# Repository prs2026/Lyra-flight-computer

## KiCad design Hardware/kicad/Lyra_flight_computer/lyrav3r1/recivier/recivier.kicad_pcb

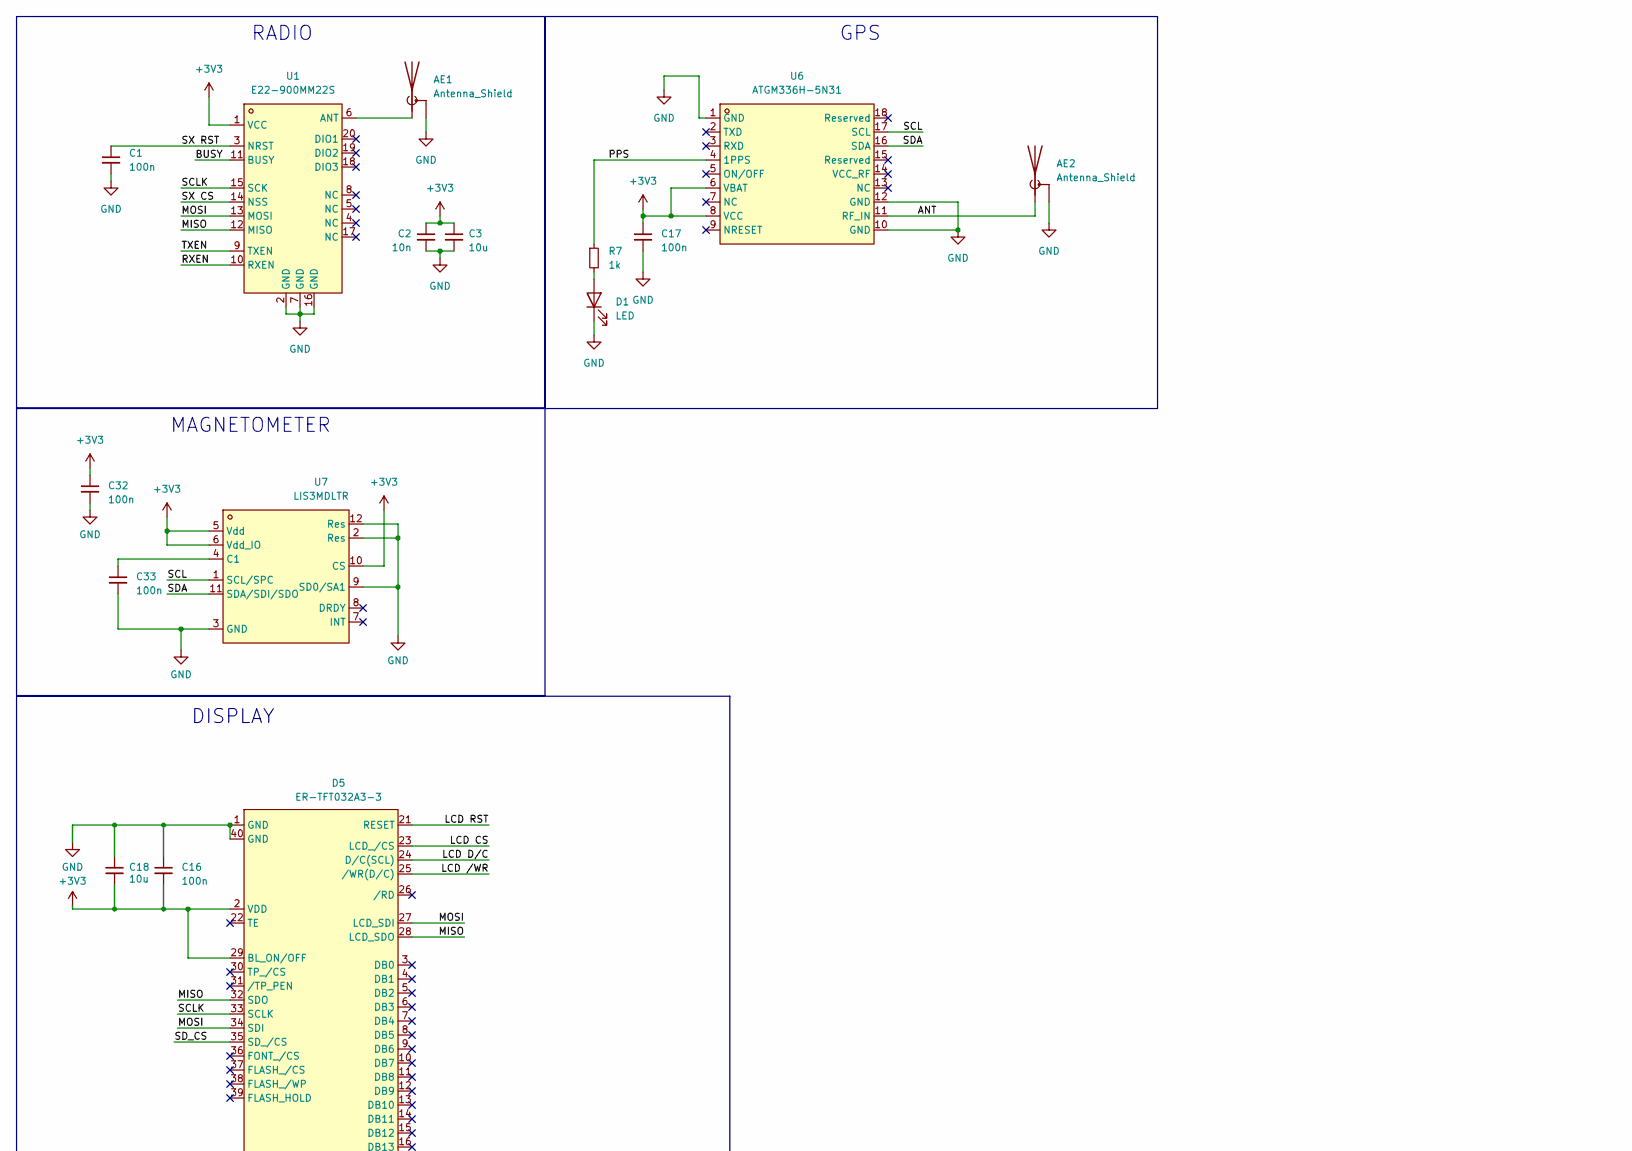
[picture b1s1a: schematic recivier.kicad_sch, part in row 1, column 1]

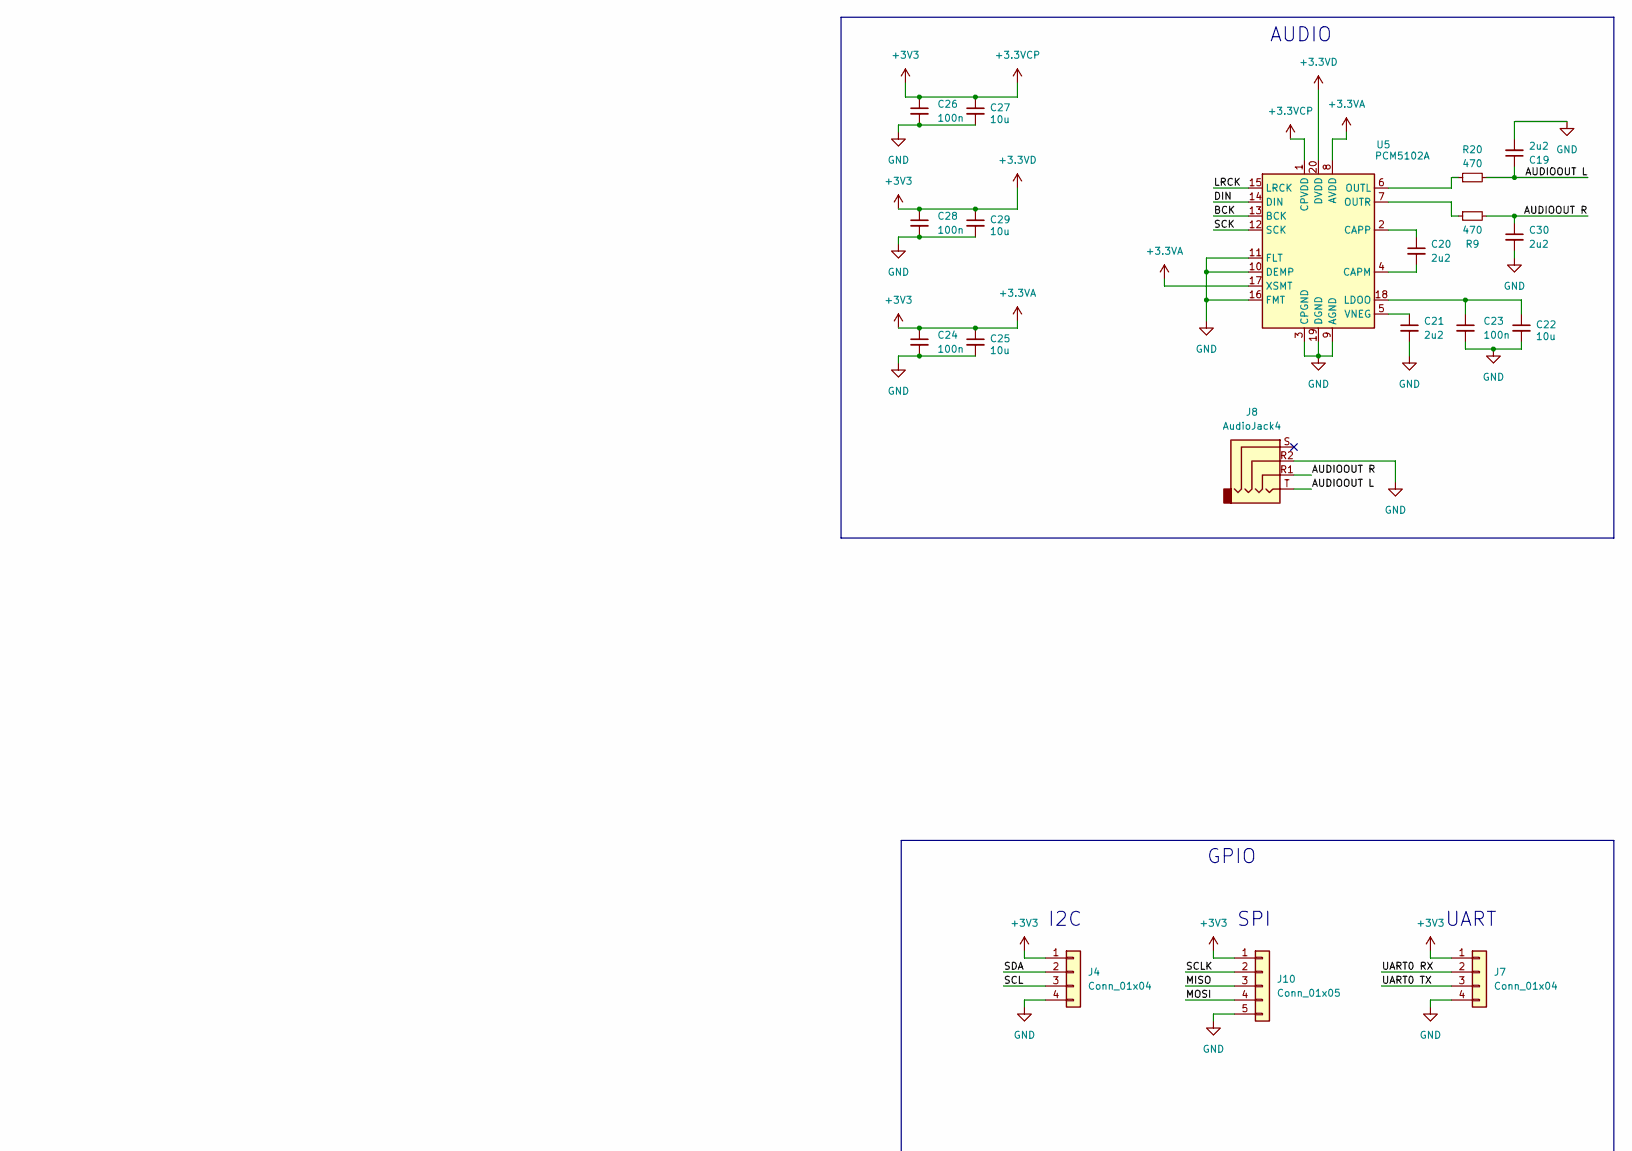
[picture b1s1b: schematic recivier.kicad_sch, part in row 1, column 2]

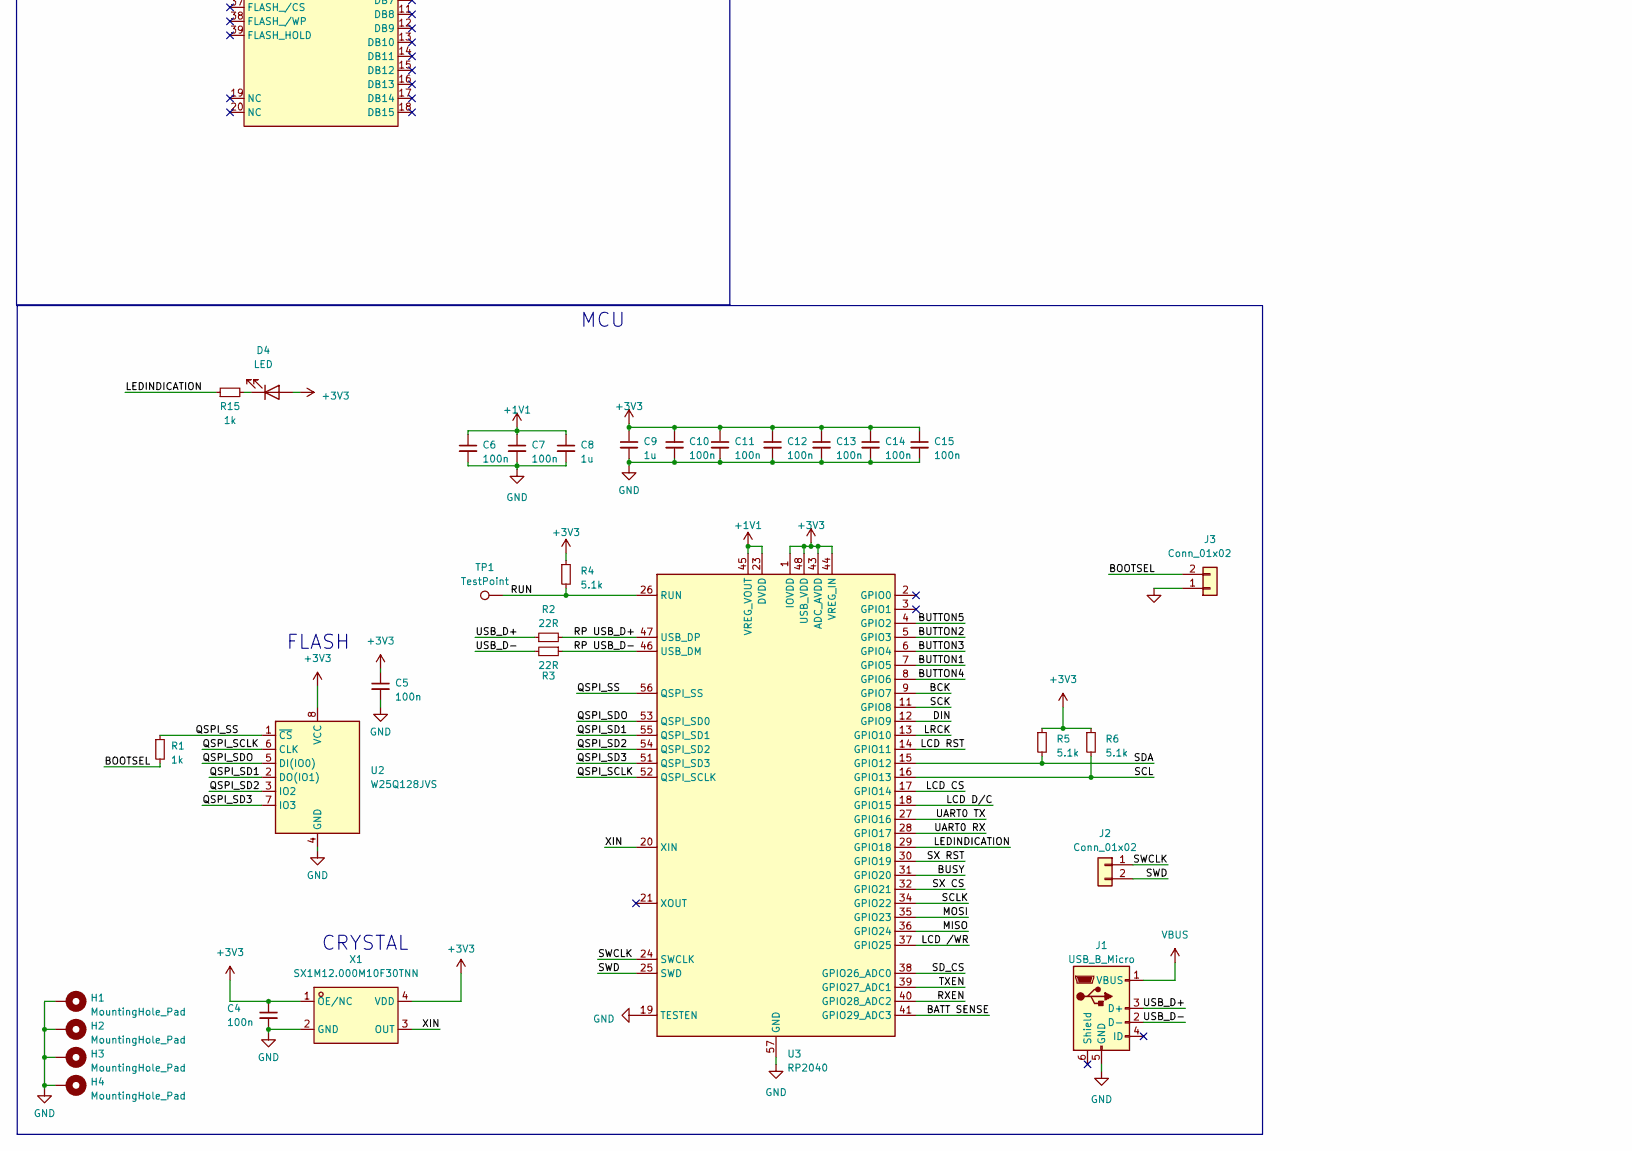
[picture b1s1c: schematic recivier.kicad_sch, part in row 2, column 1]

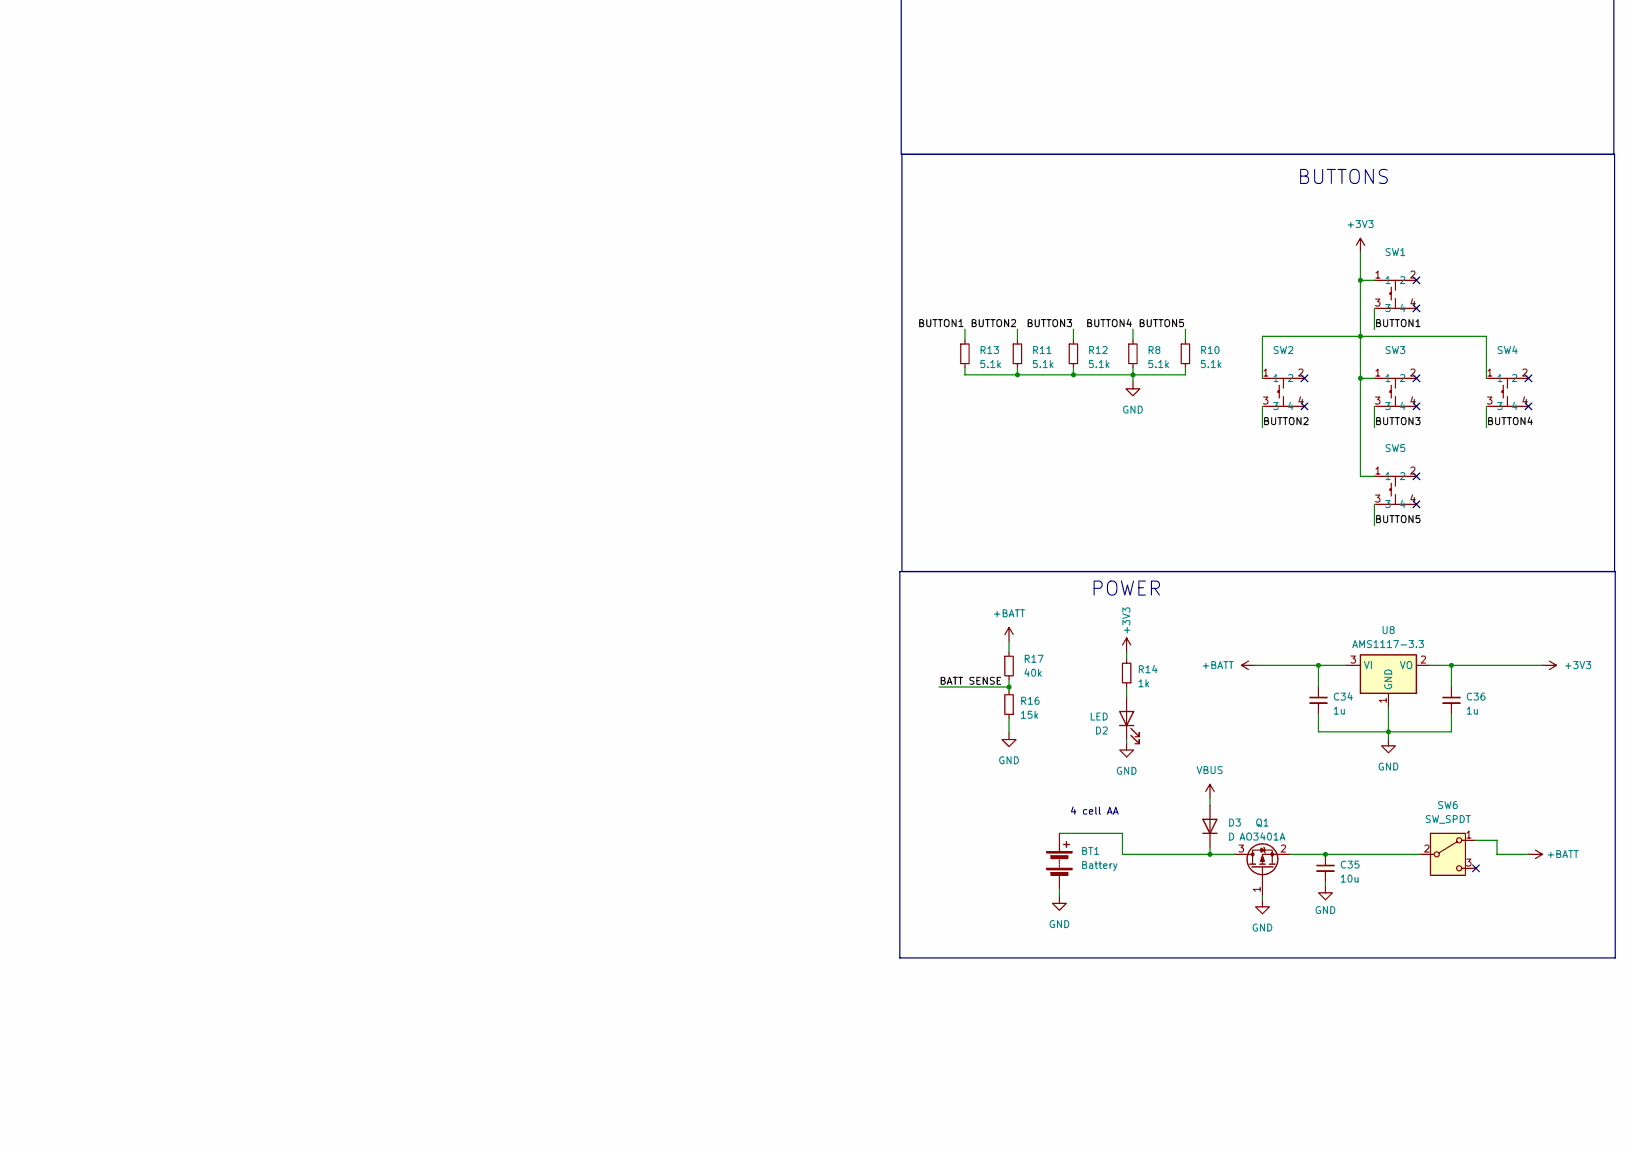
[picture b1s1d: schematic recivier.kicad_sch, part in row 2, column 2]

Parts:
AE1: Antenna_Shield; CONN-SMD_KH-SMA-KE8-G; LCSC Part C530661
AE2: Antenna_Shield; ANT-SMD_1909763-1; LCSC Part C392444
BT1: Battery; 12BH349GR
C1, C4, C5, C6, C7, C10, C11, C12, C13, C14, C15, C16, C17, C23, C24, C26, C28, C32, C33: 100n; C_0402_1005Metric; LCSC Part C1525
C2: 10n; C_0402_1005Metric; LCSC Part C15195
C3, C18, C22, C25, C27, C29, C35: 10u; C_0603_1608Metric; LCSC Part C96446
C8, C9, C34, C36: 1u; C_0402_1005Metric; LCSC Part C52923
C19, C20, C21, C30: 2u2; C_0603_1608Metric; LCSC Part C23630
D1, D2, D4: LED; LED_0805_2012Metric; LCSC Part C2297
D3: D; D_SOD-123; LCSC Part C64898
D5: ER-TFT032A3-3; R-TFT032IPS-3.2
H1, H2, H3, H4: MountingHole_Pad; MountingHole_3.2mm_M3_DIN965_Pad
J1: USB_B_Micro; MICRO-USB-SMD_U254-051T-4BHJ25-F2S; LCSC Part C381143
J2: Conn_01x02; SolderJumper-2_P1.3mm_Open_Pad1.0x1.5mm
J3: Conn_01x02; SolderJumper-2_P1.3mm_Open_RoundedPad1.0x1.5mm
J4, J7: Conn_01x04; PinHeader_1x04_P2.54mm_Horizontal
J8: AudioJack4; AUDIO-SMD_PJ-320D; LCSC Part C521460
J10: Conn_01x05; PinHeader_1x05_P2.54mm_Horizontal
Q1: AO3401A; SOT-23; LCSC Part C15127
R1, R7, R14, R15: 1k; R_0402_1005Metric; LCSC Part C11702
R2, R3: 22R; R_0402_1005Metric; LCSC Part C25092
R4, R5, R6, R8, R10, R11, R12, R13: 5.1k; R_0402_1005Metric; LCSC Part C25905
R9, R20: 470; R_0402_1005Metric; LCSC Part C25117
R16: 15k; R_0402_1005Metric; LCSC Part C25756
R17: 40k; R_0402_1005Metric; LCSC Part C25086
SW1, SW2, SW3, SW4, SW5: K2-1102DP-L3SW-04; SW-TH_4P-L6.0-W6.0-P4.50-LS6.5; LCSC Part C493026
SW6: SW_SPDT; SW-TH_SK12D07VG4; LCSC Part C393937
TP1: TestPoint; TestPoint_Pad_1.0x1.0mm
U1: E22-900MM22S; WIRELM-SMD_E22-400MM22S
U2: W25Q128JVS; SOIC-8_5.23x5.23mm_P1.27mm; LCSC Part C97521
U3: RP2040; QFN-56-1EP_7x7mm_P0.4mm_EP3.2x3.2mm; LCSC Part C2040
U5: PCM5102A; TSSOP-20_4.4x6.5mm_P0.65mm; LCSC Part C107671
U6: ATGM336H-5N31; GPSM-SMD_ATGM336H-TR; LCSC Part C90770
U7: LIS3MDLTR; LGA-12_L2.0-W2.0-P0.50-BL; LCSC Part C478483
U8: AMS1117-3.3; SOT-223-3_TabPin2; LCSC Part C6186
X1: SX1M12.000M10F30TNN; OSC-SMD_4P-L2.0-W1.6-BL; LCSC Part C2901608

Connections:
+1V1: C6.1, C7.1, C8.1, U3.23 (DVDD), U3.45 (VREG_VOUT), U3.50 (DVDD)
+3.3VA: C2.1, C3.1, C4.1, C5.1, C9.1, C10.1, C11.1, C12.1, C13.1, C14.1, C15.1, C16.2, C17.1, C18.2, C24.1, C25.1, C26.1, C27.1, C28.1, C29.1, C32.1, C36.1, D4.2 (A), D5.2 (VDD), D5.29 (BL_ON/OFF), J4.1, J7.1, J10.1, R4.1, R5.1, R6.1, R14.2, SW1.1, SW2.1, SW3.1, SW4.1, SW5.1, U1.1 (VCC), U2.8 (VCC), U3.1 (IOVDD), U3.10 (IOVDD), U3.22 (IOVDD), U3.33 (IOVDD), U3.42 (IOVDD), U3.43 (ADC_AVDD), U3.44 (VREG_IN), U3.48 (USB_VDD), U3.49 (IOVDD), U5.1 (CPVDD), U5.8 (AVDD), U5.17 (XSMT), U5.20 (DVDD), U6.6 (VBAT), U6.8 (VCC), U7.5 (Vdd), U7.6 (Vdd_IO), U7.10 (CS), U8.2 (VO), X1.1 (OE/NC), X1.4 (VDD)
+BATT: C34.1, R17.1, SW6.1 (A), U8.3 (VI)
/ANT: AE2.1 (A), U6.11 (RF_IN)
/AUDIOOUT L: C19.1, J8.T, R20.2
/AUDIOOUT R: C30.1, J8.R1, R9.2
/BATT SENSE: R16.2, R17.2, U3.41 (GPIO29_ADC3)
/BCK: U3.9 (GPIO7), U5.13 (BCK)
/BOOTSEL: J3.2, R1.2
/BUSY: U1.11 (BUSY), U3.31 (GPIO20)
/BUTTON1: R13.1, SW1.3, U3.7 (GPIO5)
/BUTTON2: R11.1, SW2.3, U3.5 (GPIO3)
/BUTTON3: R12.1, SW3.3, U3.6 (GPIO4)
/BUTTON4: R8.1, SW4.3, U3.8 (GPIO6)
/BUTTON5: R10.1, SW5.3, U3.4 (GPIO2)
/DIN: U3.12 (GPIO9), U5.14 (DIN)
/LCD CS: D5.23 (LCD_/CS), U3.17 (GPIO14)
/LCD D/C: D5.24 (D/C(SCL)), U3.18 (GPIO15)
/LCD RST: D5.21 (RESET), U3.14 (GPIO11)
/LCD /WR: D5.25 (/WR(D/C)), U3.37 (GPIO25)
/LEDINDICATION: R15.1, U3.29 (GPIO18)
/LRCK: U3.13 (GPIO10), U5.15 (LRCK)
/MISO: D5.28 (LCD_SDO), D5.32 (SDO), J10.3, U1.12 (MISO), U3.36 (GPIO24)
/MOSI: D5.27 (LCD_SDI), D5.34 (SDI), J10.4, U1.13 (MOSI), U3.35 (GPIO23)
/PPS: R7.1, U6.4 (1PPS)
/QSPI_SCLK: U2.6 (CLK), U3.52 (QSPI_SCLK)
/QSPI_SD1: U2.2 (DO(IO1)), U3.55 (QSPI_SD1)
/QSPI_SD2: U2.3 (IO2), U3.54 (QSPI_SD2)
/QSPI_SD3: U2.7 (IO3), U3.51 (QSPI_SD3)
/QSPI_SDO: U2.5 (DI(IO0)), U3.53 (QSPI_SD0)
/QSPI_SS: R1.1, U2.1 (~CS), U3.56 (QSPI_SS)
/RP USB_D+: R2.2, U3.47 (USB_DP)
/RP USB_D-: R3.1, U3.46 (USB_DM)
/RUN: R4.2, TP1.1, U3.26 (RUN)
/RXEN: U1.10 (RXEN), U3.40 (GPIO28_ADC2)
/SCK: U3.11 (GPIO8), U5.12 (SCK)
/SCL: J4.3, R6.2, U3.16 (GPIO13), U6.17 (SCL), U7.1 (SCL/SPC)
/SCLK: D5.33 (SCLK), J10.2, U1.15 (SCK), U3.34 (GPIO22)
/SDA: J4.2, R5.2, U3.15 (GPIO12), U6.16 (SDA), U7.11 (SDA/SDI/SDO)
/SD_CS: D5.35 (SD_/CS), U3.38 (GPIO26_ADC0)
/SWCLK: J2.1, U3.24 (SWCLK)
/SWD: J2.2, U3.25 (SWD)
/SX CS: U1.14 (NSS), U3.32 (GPIO21)
/SX RST: C1.1, U1.3 (NRST), U3.30 (GPIO19)
/TXEN: U1.9 (TXEN), U3.39 (GPIO27_ADC1)
/UART0 RX: J7.2, U3.28 (GPIO17)
/UART0 TX: J7.3, U3.27 (GPIO16)
/USB_D+: J1.3 (D+), R2.1
/USB_D-: J1.2 (D-), R3.2
/XIN: U3.20 (XIN), X1.3 (OUT)
GND: AE1.2 (Shield), AE2.2 (Shield), BT1.2 (-), C1.2, C2.2, C3.2, C4.2, C5.2, C6.2, C7.2, C8.2, C9.2, C10.2, C11.2, C12.2, C13.2, C14.2, C15.2, C16.1, C17.2, C18.1, C19.2, C21.2, C22.2, C23.2, C24.2, C25.2, C26.2, C27.2, C28.2, C29.2, C30.2, C32.2, C33.2, C34.2, C35.2, C36.2, D1.1 (K), D2.1 (K), D5.1 (GND), D5.40 (GND), H1.1, H2.1, H3.1, H4.1, J1.5 (GND), J3.1, J4.4, J7.4, J8.R2, J10.5, Q1.1 (G), R8.2, R10.2, R11.2, R12.2, R13.2, R16.1, U1.2 (GND), U1.7 (GND), U1.16 (GND), U2.4 (GND), U3.19 (TESTEN), U3.57 (GND), U5.3 (CPGND), U5.9 (AGND), U5.10 (DEMP), U5.11 (FLT), U5.16 (FMT), U5.19 (DGND), U6.1 (GND), U6.10 (GND), U6.12 (GND), U7.2 (Res), U7.3 (GND), U7.9 (SD0/SA1), U7.12 (Res), U8.1 (GND), X1.2 (GND)
unnamed: AE1.1 (A), U1.6 (ANT)
unnamed: BT1.1 (+), D3.1 (K), Q1.3 (D)
unnamed: D1.2 (A), R7.2
unnamed: D2.2 (A), R14.1
unnamed: D4.1 (K), R15.2
unnamed: C35.1, Q1.2 (S), SW6.2 (B)
unnamed: C20.2, U5.4 (CAPM)
unnamed: C20.1, U5.2 (CAPP)
unnamed: C22.1, C23.1, U5.18 (LDOO)
unnamed: R20.1, U5.6 (OUTL)
unnamed: R9.1, U5.7 (OUTR)
unnamed: C21.1, U5.5 (VNEG)
unnamed: C33.1, U7.4 (C1)
VBUS: D3.2 (A), J1.1 (VBUS)

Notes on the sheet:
FLASH
4 cell AA
I2C
AUDIO
MAGNETOMETER
CRYSTAL
POWER
BUTTONS
GPS
RADIO
GPIO
DISPLAY
UART
SPI
MCU

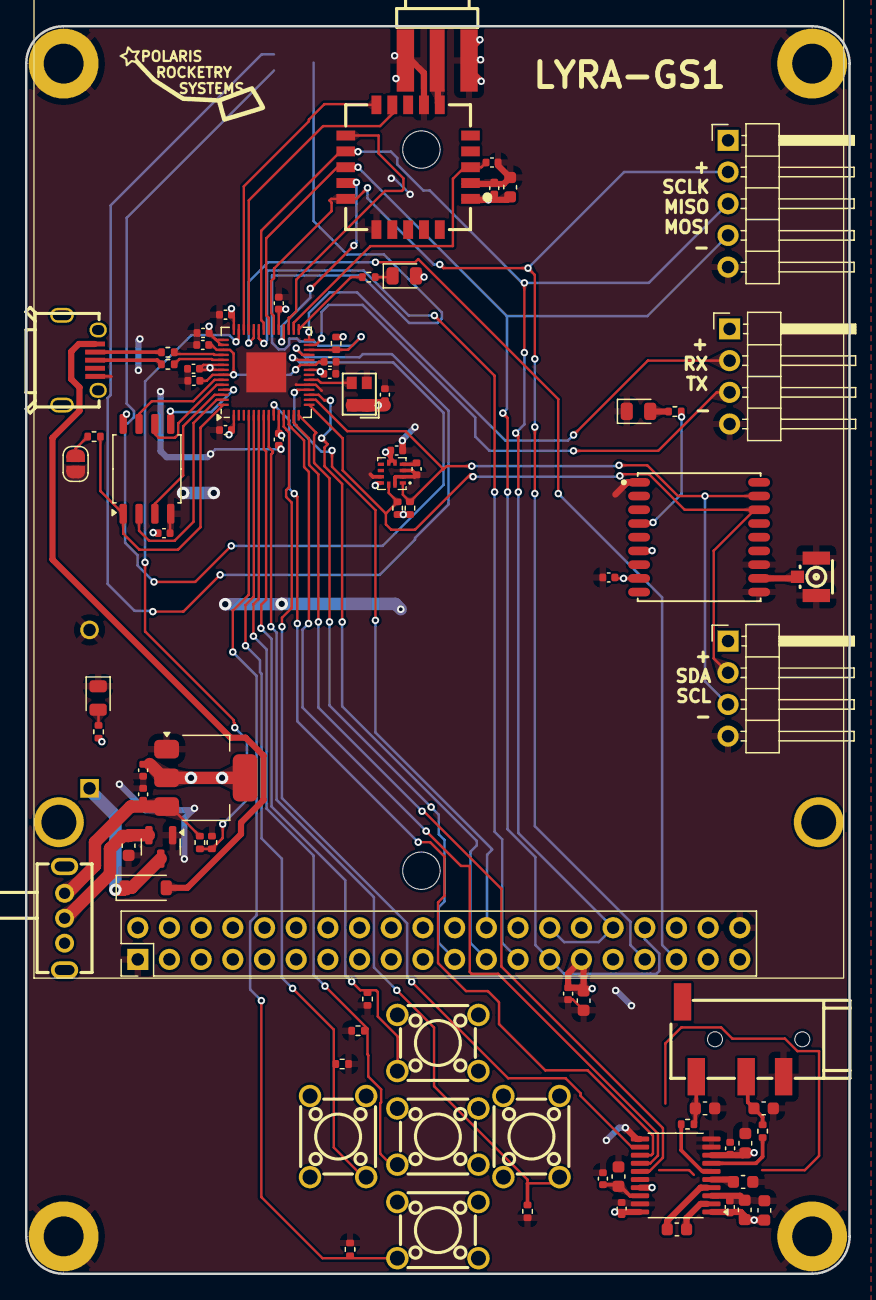
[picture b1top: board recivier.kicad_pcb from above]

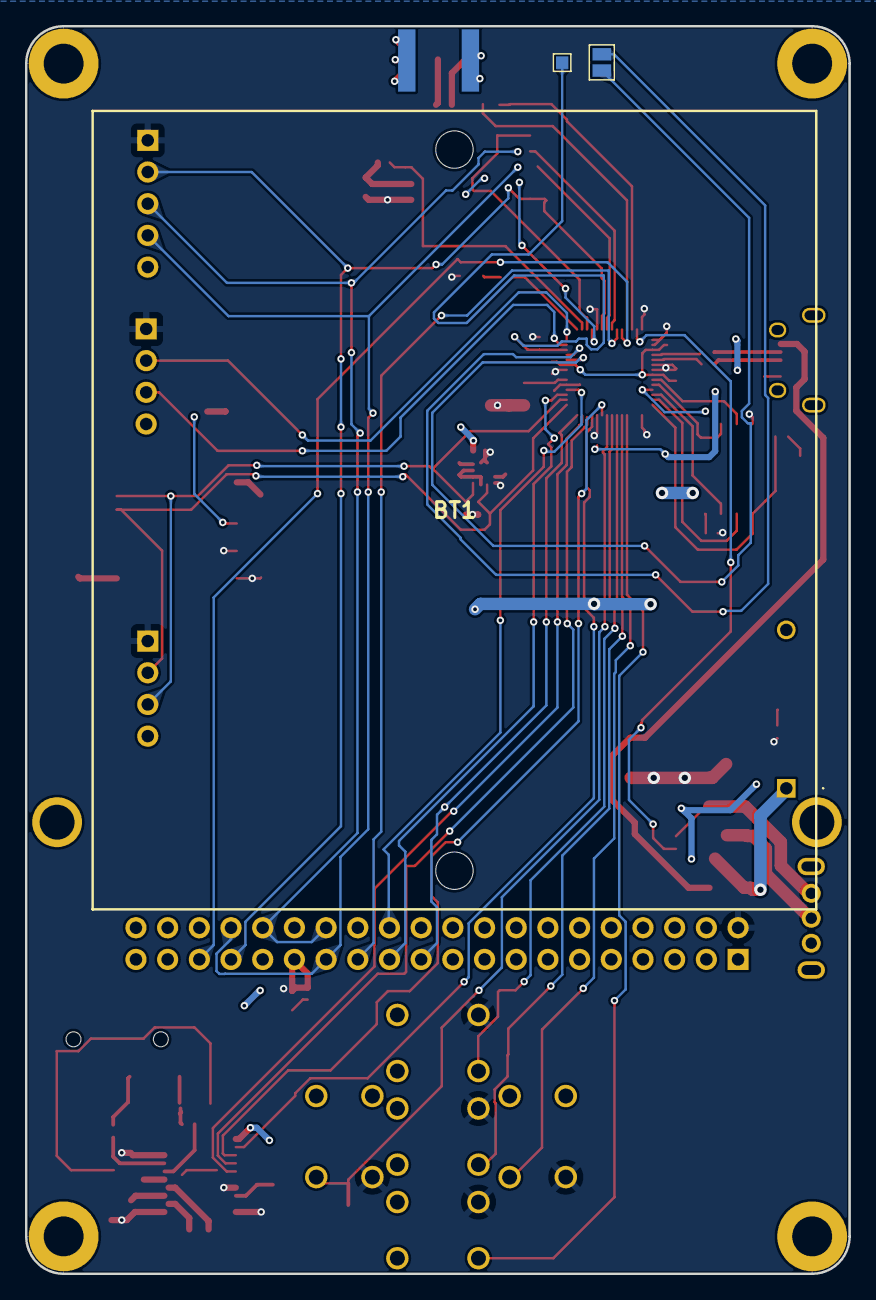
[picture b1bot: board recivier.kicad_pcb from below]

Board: 2 copper layers, 66.0 x 100.0 mm, 88 parts (3 on the bottom side), 65 nets.

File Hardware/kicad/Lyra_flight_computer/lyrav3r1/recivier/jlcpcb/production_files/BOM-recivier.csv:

Comment,Designator,Footprint,LCSC
PCM5102A,U5,TSSOP-20_4.4x6.5mm_P0.65mm,C107671
1k,"R1,R14,R15,R7",R_0402_1005Metric,C11702
AO3401A,Q1,SOT-23,C15127
10n,C2,C_0402_1005Metric,C15195
100n,"C1,C10,C11,C12,C13,C14,C15,C16,C17,C23,C24,C26,C28,C32,C33,C4,C5,C6,C7",C_0402_1005Metric,C1525
RP2040,U3,QFN-56-1EP_7x7mm_P0.4mm_EP3.2x3.2mm,C2040
LED,"D1,D2,D4",LED_0805_2012Metric,C2297
2u2,"C19,C20,C21,C30",C_0603_1608Metric,C23630
40k,R17,R_0402_1005Metric,C25086
22R,"R2,R3",R_0402_1005Metric,C25092
470,"R20,R9",R_0402_1005Metric,C25117
15k,R16,R_0402_1005Metric,C25756
5.1k,"R10,R11,R12,R13,R4,R5,R6,R8",R_0402_1005Metric,C25905
SX1M12.000M10F30TNN,X1,OSC-SMD_4P-L2.0-W1.6-BL,C2901608
USB_B_Micro,J1,MICRO-USB-SMD_U254-051T-4BHJ25-F2S,C381143
Antenna_Shield,AE2,ANT-SMD_1909763-1,C392444
SW_SPDT,SW6,SW-TH_SK12D07VG4,C393937
LIS3MDLTR,U7,LGA-12_L2.0-W2.0-P0.50-BL,C478483
K2-1102DP-L3SW-04,"SW1,SW2,SW3,SW4,SW5",SW-TH_4P-L6.0-W6.0-P4.50-LS6.5,C493026
AudioJack4,J8,AUDIO-SMD_PJ-320D,C521460
1u,"C34,C36,C8,C9",C_0402_1005Metric,C52923
Antenna_Shield,AE1,CONN-SMD_KH-SMA-KE8-G,C530661
AMS1117-3.3,U8,SOT-223-3_TabPin2,C6186
D,D3,D_SOD-123,C64898
ATGM336H-5N31,U6,GPSM-SMD_ATGM336H-TR,C90770
10u,"C18,C22,C25,C27,C29,C3,C35",C_0603_1608Metric,C96446
W25Q128JVS,U2,SOIC-8_5.23x5.23mm_P1.27mm,C97521

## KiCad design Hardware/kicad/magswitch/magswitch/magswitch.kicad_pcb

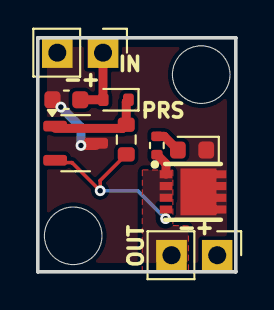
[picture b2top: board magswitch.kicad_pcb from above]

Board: 2 copper layers, 11.0 x 13.0 mm, 11 parts (0 on the bottom side), 6 nets.

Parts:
C1: 10u; C_0603_1608Metric
D1: LED; LED_0603_1608Metric
D3: D_Schottky; D_SOD-523
H1, H2: MountingHole; MountingHole_3.2mm_M3
J1, J3: Conn_01x02; PinHeader_1x02_P2.54mm_Vertical
Q1: AON7508; PQFN-8_L3.0-W3.0-P0.65-LS3.2-BL
R1: 10k; R_0603_1608Metric
R3: 10k; R_0402_1005Metric
U1: SK1816G-AE3-R; SOT-23-3

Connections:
+BATT: C1.1, D3.2 (A), J1.1, J3.1
/SENSE OUT: Q1.4 (G), R1.2, U1.2 (VOUT)
/SWITCH: J1.2, Q1.1 (S), Q1.2 (S), Q1.3 (S), R3.2
GND: C1.2, D1.1 (K), J3.2, Q1.5 (D), Q1.6 (D), Q1.7 (D), Q1.8 (D), U1.3 (GND)
unnamed: D1.2 (A), R3.1
unnamed: D3.1 (K), R1.1, U1.1 (VIN)

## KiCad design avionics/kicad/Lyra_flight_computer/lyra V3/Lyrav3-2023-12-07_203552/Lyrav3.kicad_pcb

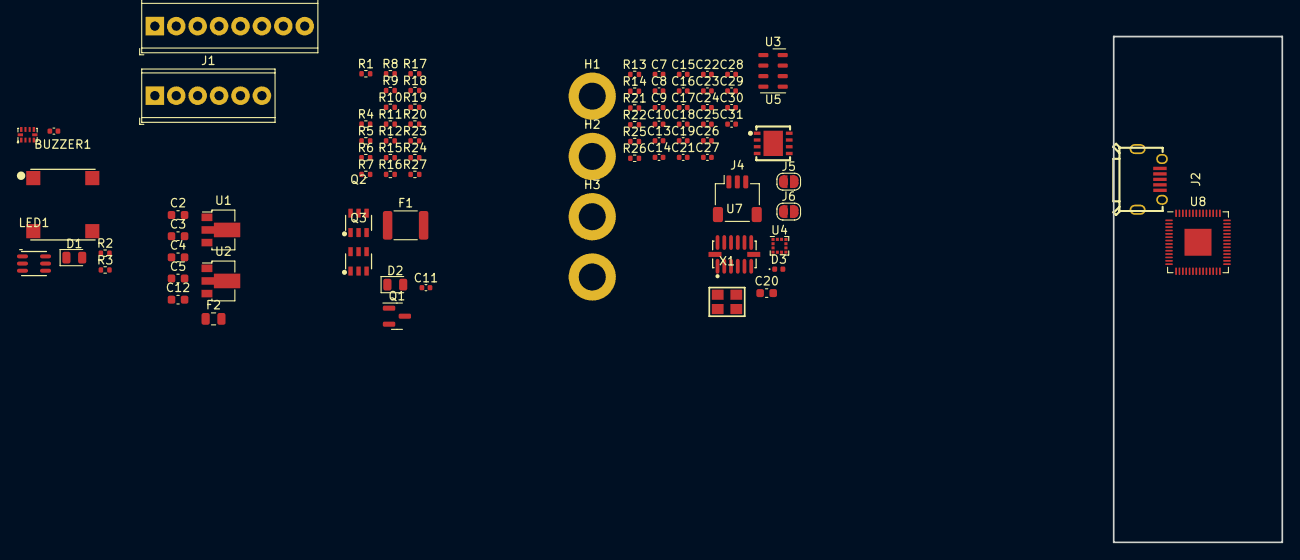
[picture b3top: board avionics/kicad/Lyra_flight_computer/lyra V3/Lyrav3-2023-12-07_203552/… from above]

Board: 4 copper layers, 20.0 x 60.0 mm, 86 parts (0 on the bottom side), 52 nets, no tracks yet.

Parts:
BUZZER1: MLT-7525; BUZ-SMD_4P-L7.5-W7.5-P7.59-TL
C1, C8, C9, C10, C16, C17, C18, C19, C21, C22, C23, C24, C25, C27, C28, C29, C30, C31: 100n; C_0402_1005Metric
C2, C3, C4, C12: 22u; C_0603_1608Metric
C5, C20: 10u; C_0603_1608Metric
C7, C11, C13, C15, C26: 1u; C_0402_1005Metric
C14: 2u2; C_0402_1005Metric
D1, D2: LED; LED_0805_2012Metric
D3: D; D_0402_1005Metric
F1: 2a; Fuse_1812_4532Metric
F2: 200ma; Fuse_0805_2012Metric
H1, H2, H3, H4: MountingHole_Pad; MountingHole_3.2mm_M3_DIN965_Pad
J1: Screw_Terminal_01x06; TerminalBlock_Phoenix_MPT-0,5-6-2.54_1x06_P2.54mm_Horizontal
J2: USB_B_Micro; MICRO-USB-SMD_U254-051T-4BHJ25-F2S
J3: Screw_Terminal_01x08; TerminalBlock_Phoenix_MPT-0,5-8-2.54_1x08_P2.54mm_Horizontal
J4: Conn_01x03; JST_SH_SM03B-SRSS-TB_1x03-1MP_P1.00mm_Horizontal
J5, J6: Conn_01x02; SolderJumper-2_P1.3mm_Open_RoundedPad1.0x1.5mm
LED1: FM-Z2727RGBA-SH; LED-SMD_6P-L2.7-W2.8-TL
Q1: AO3401A; SOT-23
Q2, Q3: KY6802; SOT-23-6_L2.9-W1.6-P0.95-LS2.8-BL
R1, R2, R3, R13: 1k; R_0402_1005Metric
R4, R5, R12, R15: 470R; R_0402_1005Metric
R6, R7, R16, R17: 10R; R_0402_1005Metric
R8, R10, R18, R20, R24: 20k; R_0402_1005Metric
R9, R11, R19, R23, R27: 6k; R_0402_1005Metric
R14, R21: 27R; R_0402_1005Metric
R22: 10k; R_0402_1005Metric
R25, R26: 2k2; R_0402_1005Metric
U1: AMS1117-3.3; SOT-89-3
U2: AMS1117-5.0; SOT-89-3
U3: MPL3115A2; NXP_LGA-8_3x5mm_P1.25mm_H1.1mm
U4: LIS3MDL; LGA-12_2x2mm_P0.5mm
U5: W25Q64JVXGIQ; XSON-8_L4.0-W4.0-P0.80-TL-EP
U7: ADXL375BCCZ-RL7; LGA-14_L5.0-W3.0-P0.80-BL
U8: RP2040; QFN-56-1EP_7x7mm_P0.4mm_EP3.2x3.2mm
U9: ADS1015IDGS; X2QFN-10_L2.0-W1.5-P0.50-BL
X1: S3D12.288000B20F30T; OSC-SMD_4P-L3.2-W2.5-BL_SIT8008BI

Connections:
+1V1: C8.1, C10.1, C13.1, U8.23 (DVDD), U8.45 (VREG_VOUT), U8.50 (DVDD)
+3V3: C1.1, C3.1, C7.1, C9.1, C14.1, C15.1, C16.1, C17.1, C18.1, C20.1, C22.1, C23.1, C24.1, C25.1, C26.1, C27.1, C28.1, C29.1, C30.1, C31.1, R1.2, R2.2, R3.2, R22.1, R25.1, R26.1, U1.2 (VO), U3.1 (VDD), U3.4 (VDDIO), U4.5 (Vdd), U4.6 (Vdd_IO), U4.10 (~CS), U5.8 (VCC), U7.1 (VDDI/O), U7.3 (RESERVED), U7.6 (VS), U7.7 (~CS), U8.1 (IOVDD), U8.10 (IOVDD), U8.22 (IOVDD), U8.33 (IOVDD), U8.42 (IOVDD), U8.43 (ADC_AVDD), U8.44 (VREG_IN), U8.48 (USB_VDD), U8.49 (IOVDD), U9.1 (ADDR), U9.8 (VDD), X1.1 (Tri-state), X1.4 (VDD)
+5VD: C12.1, U2.2 (VO)
+12P: F1.2, J1.2
+12V: J1.3, Q1.3 (D), R18.1
+12VA: C2.1, C4.1, C5.1, C11.1, F2.2, U1.3 (VI), U2.3 (VI)
+BATT: J1.4, J1.6
/Board2/BATT SENSE BOT: R18.2, R19.1
/Board2/P1 CONT BOT: R24.2, R27.1, U9.4 (AIN0)
/Board2/P1 EN BOT: Q3.1 (G), R15.2
/Board2/P2 CONT BOT: R20.2, R23.1, U9.5 (AIN1)
/Board2/P2 EN BOT: Q3.3 (G), R12.2
/Board2/P3 CONT BOT: R10.2, R11.1, U9.6 (AIN2)
/Board2/P3 EN BOT: Q2.1 (G), R5.2
/Board2/P4 CONT BOT: R8.2, R9.1, U9.7 (AIN3)
/Board2/P4 EN BOT: Q2.3 (G), R4.2
/Topboard/BOOTSEL: J6.2, R13.2
/Topboard/BUZZER: BUZZER1.1 (+), BUZZER1.4, U8.8 (GPIO6)
/Topboard/I2C0 SCL: U3.8 (SCL), U4.1 (SCL/SPC), U7.14 (SCL/SCLK), U8.7 (GPIO5)
/Topboard/I2C0 SDA: U3.7 (SDL), U4.11 (SDA/SDI/SDO), U7.13 (SDA/SDI/SDIO), U8.6 (GPIO4)
/Topboard/I2C1 SCL: R25.2, U8.35 (GPIO23)
/Topboard/I2C1 SDA: R26.2, U8.34 (GPIO22)
/Topboard/LEDBLUE: LED1.1 (-), U8.14 (GPIO11)
/Topboard/LEDGREEN: LED1.2 (-), U8.13 (GPIO10)
/Topboard/LEDRED: LED1.3 (-), U8.12 (GPIO9)
/Topboard/PYRO PWR: J1.1, J3.2, J3.4, J3.6, J3.8
/Topboard/QSPI_SCLK: U5.6 (CLK), U8.52 (QSPI_SCLK)
/Topboard/QSPI_SD1: U5.2 (DO(IO1)), U8.55 (QSPI_SD1)
/Topboard/QSPI_SD2: U5.3 (IO2), U8.54 (QSPI_SD2)
/Topboard/QSPI_SD3: U5.7 (IO3), U8.51 (QSPI_SD3)
/Topboard/QSPI_SDO: U5.5 (DI(IO0)), U8.53 (QSPI_SD0)
/Topboard/QSPI_SS: R13.1, U5.1 (~CS), U8.56 (QSPI_SS)
/Topboard/RP USB_D+: R14.2, U8.47 (USB_DP)
/Topboard/RP USB_D-: R21.1, U8.46 (USB_DM)
/Topboard/RUN: J5.1, R22.2, U8.26 (RUN)
/Topboard/SWCLK: J4.1, U8.24 (SWCLK)
/Topboard/SWD: J4.3, U8.25 (SWD)
/Topboard/USB_D+: J2.3 (D+), R14.1
/Topboard/USB_D-: J2.2 (D-), R21.2
/Topboard/XIN: U8.20 (XIN), X1.3 (OUTPUT)
GND: BUZZER1.2 (-), BUZZER1.3, C1.2, C2.2, C3.2, C4.2, C5.2, C7.2, C8.2, C9.2, C10.2, C11.2, C12.2, C13.2, C14.2, C15.2, C16.2, C17.2, C18.2, C19.2, C20.2, C21.2, C22.2, C23.2, C24.2, C25.2, C26.2, C27.2, C28.2, C29.2, C30.2, C31.2, D1.1 (K), D2.1 (K), H1.1, H2.1, H3.1, H4.1, J1.5, J2.5 (GND), J4.2, J5.2, J6.1, Q1.1 (G), Q2.2 (S), Q2.5 (S), Q3.2 (S), Q3.5 (S), R4.1, R5.1, R9.2, R11.2, R12.1, R15.1, R19.2, R23.2, R27.2, U1.1 (GND), U2.1 (GND), U3.3 (GND), U4.2 (GND), U4.3 (GND), U4.9 (SDO/SA1), U4.12 (GND), U5.4 (GND), U7.2 (GND), U7.4 (GND), U7.5 (GND), U7.11 (RESERVED), U7.12 (SDO/ALTADDRESS), U8.19 (TESTEN), U8.57 (GND), U9.3 (GND), X1.2 (GND)
unnamed: D1.2 (A), R3.1
unnamed: D2.2 (A), R1.1
unnamed: D3.2 (A), J2.1 (VBUS)
unnamed: LED1.4 (+), LED1.5 (+), LED1.6 (+), R2.1
unnamed: F1.1, F2.1, Q1.2 (S)
unnamed: Q2.6 (D), R7.2, R10.1
unnamed: Q2.4 (D), R6.2, R8.1
unnamed: Q3.6 (D), R17.2, R24.1
unnamed: Q3.4 (D), R16.2, R20.1
unnamed: C21.1, U3.2 (CAP)
unnamed: C19.1, U4.4 (C1)

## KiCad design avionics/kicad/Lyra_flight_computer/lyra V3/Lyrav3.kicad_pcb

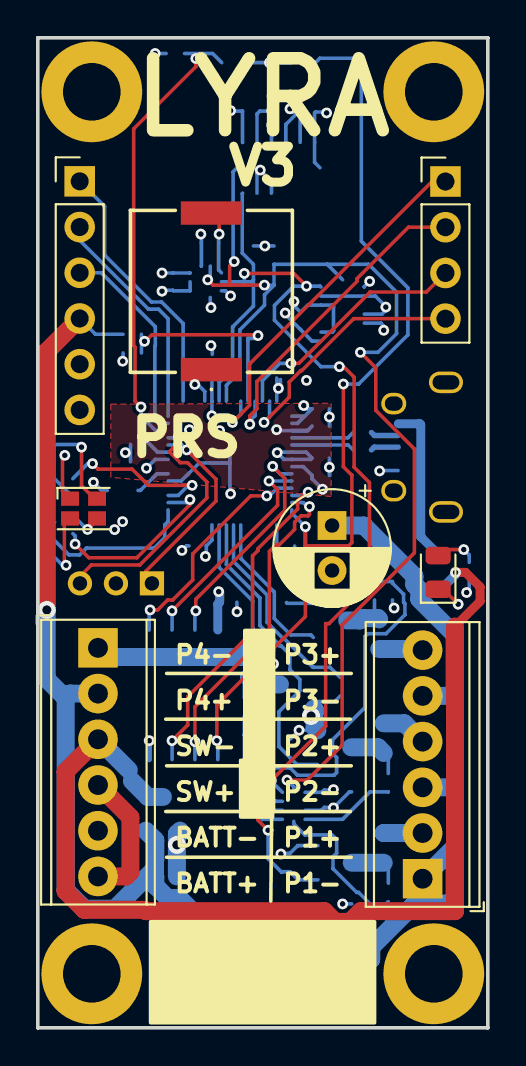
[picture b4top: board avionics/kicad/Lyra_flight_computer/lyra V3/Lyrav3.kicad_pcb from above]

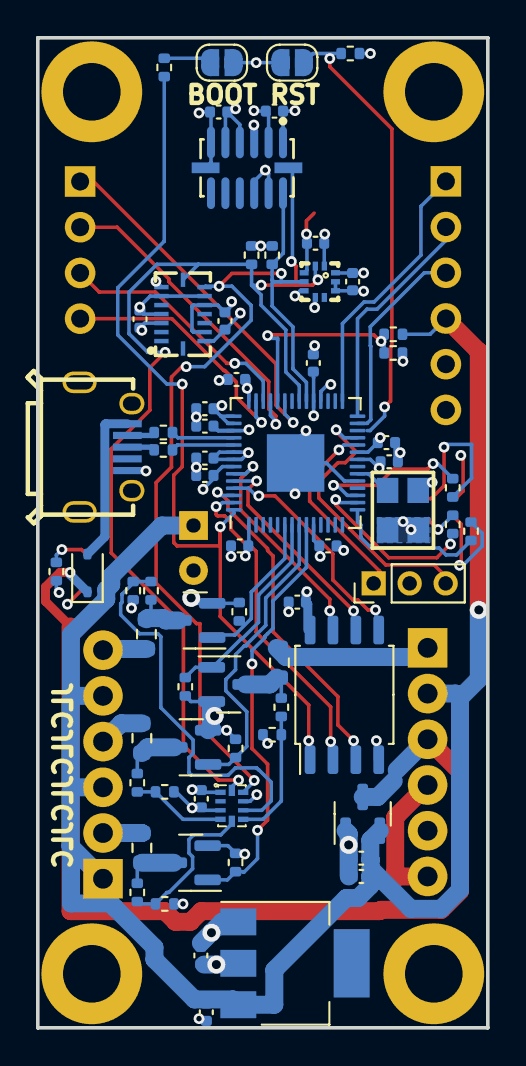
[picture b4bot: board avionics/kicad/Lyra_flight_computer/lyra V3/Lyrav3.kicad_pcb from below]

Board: 4 copper layers, 25.0 x 55.0 mm, 80 parts (68 on the bottom side), 56 nets.

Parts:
C1, C2, C4, C11, C12, C15, C16, C17, C21, C22, C23, C24, C25, C26, C27: 100n; C_0402_1005Metric
C5, C6, C7: 10u; C_0402_1005Metric
C8, C10, C18, C19: 1u; C_0402_1005Metric
C9: 680uf; CP_Radial_D6.3mm_P2.50mm
D1: D; D_SOD-323
D2: LED; LED_0805_2012Metric
D4: LED_ARGB; LED_Cree-PLCC4_2x2mm_CCW
H1, H2, H3, H4: MountingHole_Pad; MountingHole_3.2mm_M3_DIN965_Pad
J2, J9: Screw_Terminal_01x06; TerminalBlock_Phoenix_MPT-0,5-6-2.54_1x06_P2.54mm_Horizontal
J3, J4: Conn_01x02; SolderJumper-2_P1.3mm_Open_RoundedPad1.0x1.5mm
J5: Conn_01x03; PinHeader_1x03_P2.00mm_Vertical
J6: Conn_01x06; PinHeader_1x06_P2.54mm_Vertical
J7: USB_B_Micro; MICRO-USB-SMD_U254-051T-4BHJ25-F2S
J8: Conn_01x04; PinHeader_1x04_P2.54mm_Vertical
LS1: PKMCS0909E4000-R1; PKMCS0909E4000R1
Q1: AO3401A; SOT-23
Q2, Q3, Q4, Q5: AO3400A; SOT-23
R1, R5, R12, R13, R24, R25: 5.1k; R_0402_1005Metric
R2, R3, R14, R16, R17, R22, R26, R27, R28: 1k; R_0402_1005Metric
R4, R10, R11, R21, R23: 15k; R_0402_1005Metric
R6, R7: 2k2; R_0402_1005Metric
R8, R9, R19, R20: 1R; R_0603_1608Metric
R15, R18: 22R; R_0402_1005Metric
U1: AZ1117-3.3; SOT-223
U2: BMI088; LGA-16_L4.5-W3.0-P0.50-BL
U3: BMP388; SENSORM-SMD_BMP388
U4: ADXL375BCCZ-RL7; LGA-14_L5.0-W3.0-P0.80-BL
U6: ADS1015IDGS; X2QFN-10_L2.0-W1.5-P0.50-BL
U8: RP2040; QFN-56-1EP_7x7mm_P0.4mm_EP3.2x3.2mm
U9: W25Q128JVS; SOIC-8_5.23x5.23mm_P1.27mm
X1: S3D12.288000B20F30T; OSC-SMD_4P-L3.2-W2.5-BL_SIT8008BI

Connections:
+1V1: C16.1, C17.1, C18.1, U8.23 (DVDD), U8.45 (VREG_VOUT), U8.50 (DVDD)
+3V3: C1.1, C2.1, C4.1, C6.1, C10.1, C11.1, C12.1, C15.1, C19.1, C21.1, C22.1, C23.1, C24.1, C25.1, C26.1, C27.1, D4.1 (A), J6.5, R1.1, R3.2, R6.1, R7.1, U1.2 (VO), U2.3 (VDD), U2.7 (PS), U2.11 (VDDIO), U2.14 (CSB1), U3.1 (VDDIO), U3.6 (CSB), U3.10 (VDD), U4.1 (VDDI/O), U4.3 (RESERVED), U4.6 (VS), U4.7 (~CS), U6.1 (ADDR), U6.8 (VDD), U8.1 (IOVDD), U8.10 (IOVDD), U8.22 (IOVDD), U8.33 (IOVDD), U8.42 (IOVDD), U8.43 (ADC_AVDD), U8.44 (VREG_IN), U8.48 (USB_VDD), U8.49 (IOVDD), U9.8 (VCC), X1.1 (Tri-state), X1.4 (VDD)
+12P: C5.1, C7.1, C8.1, C9.1, J2.2, J6.4, J9.1, J9.3, J9.5, Q1.2 (S), R4.1, U1.3 (VI)
+12V: D1.1 (K), J2.3, Q1.3 (D)
+BATT: J2.4, J2.6
/BATT SENSE: R4.2, R5.1, U8.38 (GPIO26_ADC0)
/BOOTSEL: J4.2, R14.2
/BRKOUT1: J8.1, U8.37 (GPIO25)
/BRKOUT2: J8.2, U8.39 (GPIO27_ADC1)
/BRKOUT3: J8.3, U8.40 (GPIO28_ADC2)
/BRKOUT4: J8.4, U8.41 (GPIO29_ADC3)
/BRKOUT5: J6.3, U8.27 (GPIO16)
/BRKOUT6: J6.2, U8.28 (GPIO17)
/BRKOUT7: J6.1, U8.29 (GPIO18)
/BUZZER: LS1.1 (+), U8.32 (GPIO21)
/I2C1 SCL: R6.2, U2.8 (SCL/SCK), U3.2 (SCK), U4.14 (SCL/SCLK), U6.10 (SCL), U8.35 (GPIO23)
/I2C1 SDA: R7.2, U2.9 (SDA/SDI), U3.4 (SDI), U4.13 (SDA/SDI/SDIO), U6.9 (SDA), U8.34 (GPIO22)
/LEDBLUE: R28.1, U8.17 (GPIO14)
/LEDGREEN: R22.1, U8.16 (GPIO13)
/LEDRED: R2.1, U8.15 (GPIO12)
/P1 CONT: R10.2, R12.1, U6.5 (AIN1)
/P1 EN: Q3.1 (G), R16.2, U8.9 (GPIO7)
/P1-: J9.2, R8.1
/P2 CONT: R21.2, R24.1, U6.4 (AIN0)
/P2 EN: Q2.1 (G), R26.2, U8.8 (GPIO6)
/P2-: J9.4, R19.1
/P3 CONT: R11.2, R13.1, U6.7 (AIN3)
/P3 EN: Q4.1 (G), R17.2, U8.6 (GPIO4)
/P3-: J9.6, R9.1
/P4 CONT: R23.2, R25.1, U6.6 (AIN2)
/P4 EN: Q5.1 (G), R27.2, U8.7 (GPIO5)
/P4-: J2.1, R20.1
/QSPI_SCLK: U8.52 (QSPI_SCLK), U9.6 (CLK)
/QSPI_SD1: U8.55 (QSPI_SD1), U9.2 (DO(IO1))
/QSPI_SD2: U8.54 (QSPI_SD2), U9.3 (IO2)
/QSPI_SD3: U8.51 (QSPI_SD3), U9.7 (IO3)
/QSPI_SDO: U8.53 (QSPI_SD0), U9.5 (DI(IO0))
/QSPI_SS: R14.1, U8.56 (QSPI_SS), U9.1 (~CS)
/RP USB_D+: R15.2, U8.47 (USB_DP)
/RP USB_D-: R18.1, U8.46 (USB_DM)
/RUN: J3.1, R1.2, U8.26 (RUN)
/SWCLK: J5.1, U8.24 (SWCLK)
/SWD: J5.3, U8.25 (SWD)
/USB_D+: J7.3 (D+), R15.1
/USB_D-: J7.2 (D-), R18.2
/XIN: U8.20 (XIN), X1.3 (OUTPUT)
GND: C1.2, C2.2, C4.2, C5.2, C6.2, C7.2, C8.2, C9.2, C10.2, C11.2, C12.2, C15.2, C16.2, C17.2, C18.2, C19.2, C21.2, C22.2, C23.2, C24.2, C25.2, C26.2, C27.2, D2.1 (K), H1.1, H2.1, H3.1, H4.1, J2.5, J3.2, J4.1, J5.2, J6.6, J7.5 (GND), LS1.2 (-), Q1.1 (G), Q2.2 (S), Q3.2 (S), Q4.2 (S), Q5.2 (S), R5.2, R12.2, R13.2, R16.1, R17.1, R24.2, R25.2, R26.1, R27.1, U1.1 (GND), U2.4 (GNDA), U2.6 (GNDIO), U2.10 (SDO2), U2.15 (SDO1), U3.3 (VSS), U3.5 (SDO), U3.8 (VSS), U3.9 (VSS), U4.2 (GND), U4.4 (GND), U4.5 (GND), U4.11 (RESERVED), U4.12 (SDO/ALTADDRESS), U6.3 (GND), U8.19 (TESTEN), U8.57 (GND), U9.4 (GND), X1.2 (GND)
unnamed: D2.2 (A), R3.1
unnamed: D4.4 (BK), R28.2
unnamed: D4.3 (GK), R22.2
unnamed: D4.2 (RK), R2.2
unnamed: Q2.3 (D), R19.2, R21.1
unnamed: Q3.3 (D), R8.2, R10.1
unnamed: Q4.3 (D), R9.2, R11.1
unnamed: Q5.3 (D), R20.2, R23.1
VBUS: D1.2 (A), J7.1 (VBUS)
